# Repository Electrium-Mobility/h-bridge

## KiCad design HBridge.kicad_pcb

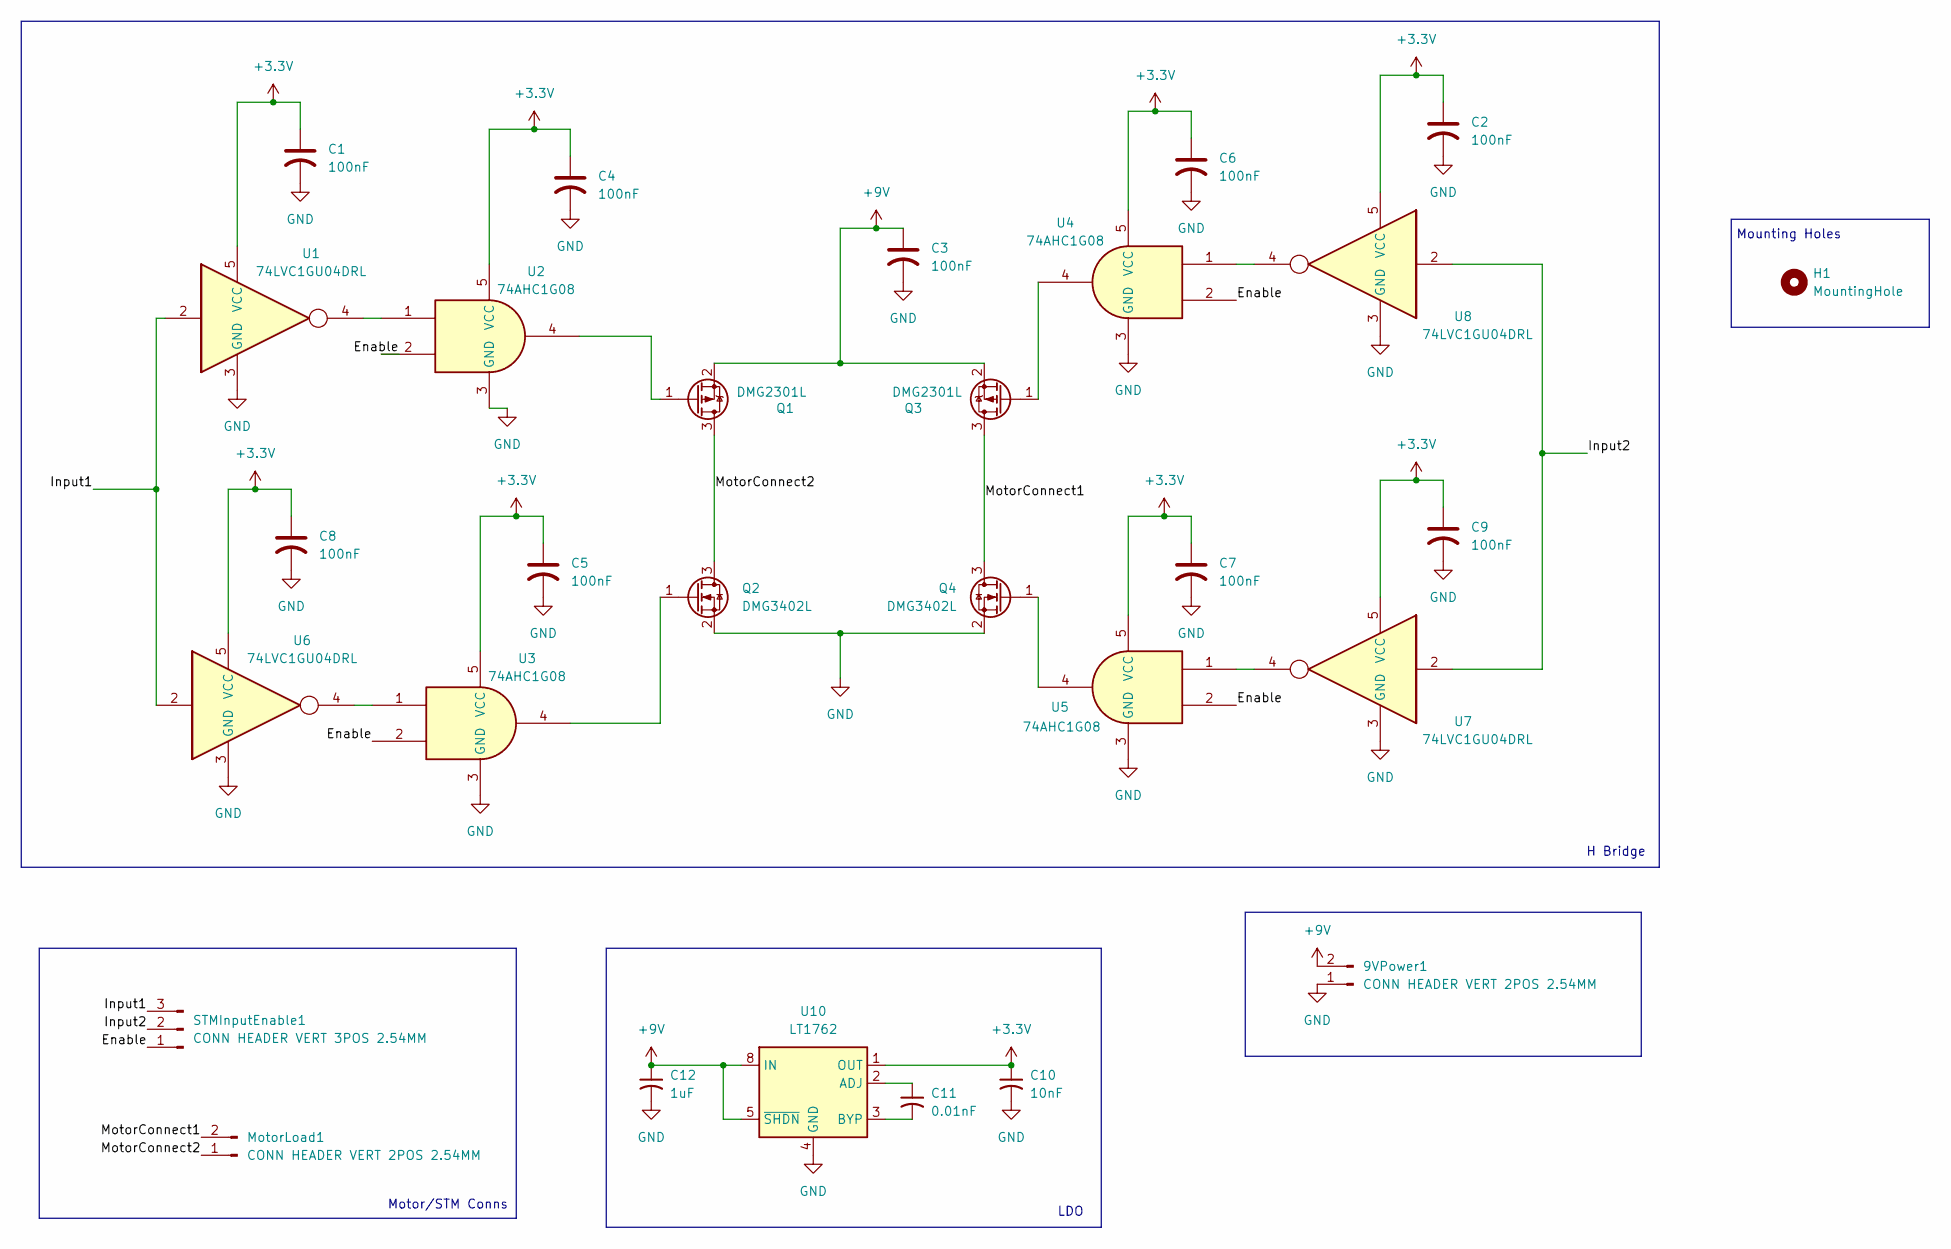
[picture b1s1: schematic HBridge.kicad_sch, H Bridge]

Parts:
9VPower1: CONN HEADER VERT 2POS 2.54MM; PinHeader_1x02_P2.54mm_Vertical
C1, C2, C3, C4, C5, C6, C7, C8, C9: 100nF; C_0603_1608Metric
C10: 10nF; C_0603_1608Metric
C11: 0.01nF; C_0603_1608Metric
C12: 1uF; C_0603_1608Metric
H1: MountingHole; MountingHole_2.5mm
MotorLoad1: CONN HEADER VERT 2POS 2.54MM; PinHeader_1x02_P2.54mm_Vertical
Q1, Q3: DMG2301L; SOT-23
Q2, Q4: DMG3402L; SOT-23
STMInputEnable1: CONN HEADER VERT 3POS 2.54MM; PinHeader_1x03_P2.54mm_Vertical
U1, U6, U7, U8: 74LVC1GU04DRL; SOT-553
U2, U3, U4, U5: 74AHC1G08; SOT-23-5
U10: LT1762; MSOP-8_3x3mm_P0.65mm

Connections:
+3.3V: C1.1, C2.1, C4.1, C5.1, C6.1, C7.1, C8.1, C9.1, C10.1, U1.5 (VCC), U2.5 (VCC), U3.5 (VCC), U4.5 (VCC), U5.5 (VCC), U6.5 (VCC), U7.5 (VCC), U8.5 (VCC), U10.1 (OUT)
+9V: 9VPower1.2, C3.1, C12.1, Q1.2 (S), Q3.2 (S), U10.5 (~SHDN), U10.8 (IN)
/Enable: STMInputEnable1.1, U2.2, U3.2, U4.2, U5.2
/Input1: STMInputEnable1.3, U1.2, U6.2
/Input2: STMInputEnable1.2, U7.2, U8.2
/MotorConnect1: MotorLoad1.2, Q3.3 (D), Q4.3 (D)
/MotorConnect2: MotorLoad1.1, Q1.3 (D), Q2.3 (D)
GND: 9VPower1.1, C1.2, C2.2, C3.2, C4.2, C5.2, C6.2, C7.2, C8.2, C9.2, C10.2, C12.2, Q2.2 (S), Q4.2 (S), U1.3 (GND), U2.3 (GND), U3.3 (GND), U4.3 (GND), U5.3 (GND), U6.3 (GND), U7.3 (GND), U8.3 (GND), U10.4 (GND)
unnamed: Q1.1 (G), U2.4
unnamed: Q2.1 (G), U3.4
unnamed: Q3.1 (G), U4.4
unnamed: Q4.1 (G), U5.4
unnamed: U1.4, U2.1
unnamed: U3.1, U6.4
unnamed: U4.1, U8.4
unnamed: U5.1, U7.4
unnamed: C11.1, U10.2 (ADJ)
unnamed: C11.2, U10.3 (BYP)

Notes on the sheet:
Motor/STM Conns
LDO
Mounting Holes
H Bridge

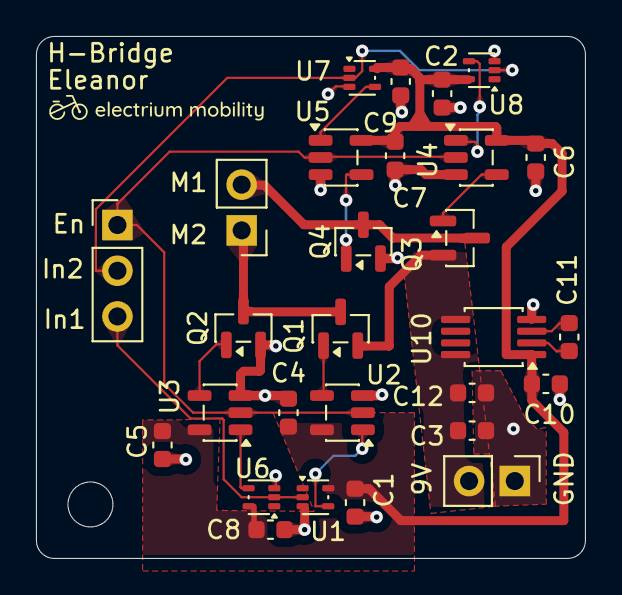
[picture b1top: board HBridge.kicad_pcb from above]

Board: 2 copper layers, 30.5 x 29.0 mm, 29 parts (0 on the bottom side), 18 nets.

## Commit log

2026-05-05 h bridge schematic
2026-05-05 h bridge hardware logic and fets
2026-05-06 nmos and pmos hw logic schematic
2026-05-08 layout
2026-05-09 fixed layout and added some routing
2026-05-09 finished routing
2026-05-09 layout and routing version 1
2026-05-09 layout and routing version 2
2026-05-12 final revisions for layout
2026-05-14 added capacitor datasheets
